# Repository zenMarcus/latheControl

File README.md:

# latheControl
lathe controller and HMI for cowells restoration project

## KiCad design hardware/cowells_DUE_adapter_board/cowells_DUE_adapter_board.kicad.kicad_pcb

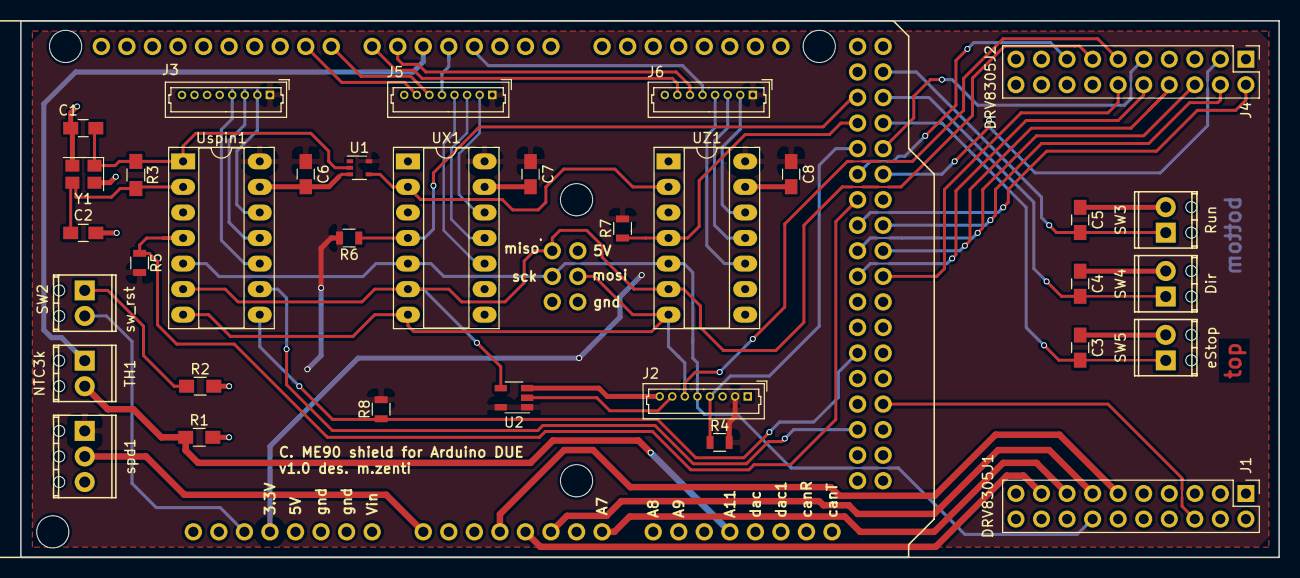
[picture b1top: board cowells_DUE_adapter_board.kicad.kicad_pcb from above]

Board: 2 copper layers, 125.1 x 53.3 mm, 35 parts (0 on the bottom side), 52 nets.

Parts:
C1, C2: 18p; C_0805_HandSoldering
C3, C4, C5: 15n; C_0805_HandSoldering
C6, C7, C8: 0.1uF; C_0805_HandSoldering
J1: DRV8305J1; Pin_Header_Straight_2x10_Pitch2.54mm
J2: AS5048A; Molex_PicoBlade_53047-0810_08x1.25mm_Straight
J3: spindl enc.; Molex_PicoBlade_53047-0810_08x1.25mm_Straight
J4: DRV8305J2; Pin_Header_Straight_2x10_Pitch2.54mm
J5, J6: AS5311AB; Molex_PicoBlade_53047-0810_08x1.25mm_Straight
R1: 1k; R_0805_HandSoldering
R2: 10k; R_0805_HandSoldering
R3: 1M; R_0805_HandSoldering
R4, R5, R6, R7, R8: 10k; R_0805
SW2: sw_rst; TerminalBlock_Phoenix_MPT-2.54mm_2pol
SW3: Run; TerminalBlock_Phoenix_MPT-2.54mm_2pol
SW4: Dir; TerminalBlock_Phoenix_MPT-2.54mm_2pol
SW5: eStop; TerminalBlock_Phoenix_MPT-2.54mm_2pol
TH1: NTC3k; TerminalBlock_Phoenix_MPT-2.54mm_2pol
U1: NL17SZ14; SOT-353_SC-70-5
U2: 74AHC1G125; TSOT-23-5
UX1: LS7366R; DIP-14_W7.62mm_Socket_LongPads
UZ1: LS7366R; DIP-14_W7.62mm_Socket_LongPads
Uspin1: LS7366R; DIP-14_W7.62mm_Socket_LongPads
XA1: Arduino_Due_Shield; Arduino_Due_Shield_drv8305
Y1: 10MHz; Crystal_SMD_3225-4pin_3.2x2.5mm
spd1: 5k; TerminalBlock_Phoenix_MPT-2.54mm_3pol

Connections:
/ClkX: J5.6, XA1.D8
/ClkZ: J6.6, XA1.D6
/CsnMot: J2.4, R4.1, XA1.D28
/CsnX: J5.5, XA1.D4
/CsnZ: J6.5, XA1.D3
/DoX: J5.7, XA1.D9
/DoZ: J6.7, XA1.D7
/ENGate: J4.15, XA1.D30
/InH_A: J4.2, XA1.D34
/InH_B: J4.6, XA1.D36
/InH_C: J4.10, XA1.D38
/InL_A: J4.4, XA1.D35
/InL_B: J4.8, XA1.D37
/InL_C: J4.12, XA1.D39
/IsenA: J1.13, XA1.A5
/IsenB: J1.15, XA1.A7
/IsenC: J1.17, XA1.A4
/MISO: J4.13, U2.4, UX1.6, UZ1.6, Uspin1.6, XA1.MISO
/MOSI: J2.6, J4.11, UX1.7, UZ1.7, Uspin1.7, XA1.MOSI
/PWRGD: J4.9, XA1.D29
/SCK: J1.14, J2.5, UX1.5, UZ1.5, Uspin1.5, XA1.SCK
/SCS: J4.3, XA1.D31
/SS_spin: R5.1, Uspin1.4, XA1.D32
/SS_x: R6.1, UX1.4, XA1.D24
/SS_z: R7.1, UZ1.4, XA1.D26
/SpnDFLAG: Uspin1.9, XA1.D50
/SpnLFLAG: R8.1, Uspin1.8, XA1.D44
/TH1: R1.1, TH1.2, XA1.A11
/Th1Ex: TH1.1, XA1.D5
/Vsen_PVDD: J1.11, XA1.A3
/nFAULT: J1.6, XA1.D49
/speed: XA1.A0, spd1.2
GND: C1.2, C2.2, C3.1, C4.1, C5.1, C6.2, C7.2, C8.2, J1.3, J2.8, J3.6, J3.8, J4.1, J5.8, J6.8, R1.2, R2.2, SW3.2, SW4.2, SW5.2, U1.3, U2.3, UX1.3, UX1.13, UZ1.3, UZ1.13, Uspin1.3, Uspin1.13, XA1.GND1, XA1.GND2, XA1.GND3, XA1.GND4, XA1.GND5, XA1.GND6, Y1.2, Y1.4, spd1.3
unnamed: C1.1, R3.1, U1.2, Uspin1.1, Y1.1
unnamed: C2.1, R3.2, Uspin1.2, Y1.3
unnamed: C3.2, SW5.1, XA1.D27
unnamed: C4.2, SW4.1, XA1.D25
unnamed: C5.2, SW3.1, XA1.D23
unnamed: J2.7, U2.2
unnamed: J3.2, Uspin1.12
unnamed: J3.3, Uspin1.11
unnamed: J3.4, Uspin1.10
unnamed: J5.2, UX1.12
unnamed: J5.3, UX1.11
unnamed: J5.4, UX1.10
unnamed: J6.2, UZ1.12
unnamed: J6.3, UZ1.11
unnamed: J6.4, UZ1.10
unnamed: R2.1, SW2.1
unnamed: SW2.2, XA1.RST1
unnamed: U1.4, UX1.2, UZ1.2
VCC: C6.1, C7.1, C8.1, J2.2, J3.1, J5.1, J6.1, R4.2, R5.2, R6.2, R7.2, R8.2, U1.5, U2.1, U2.5, UX1.14, UZ1.14, Uspin1.14, XA1.3V3, spd1.1

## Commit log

2018-02-26 first commit
    all project files
2018-05-10 implemented current reading
    current reading updated
2019-03-10 total refactor for platform IO
2019-03-10 as5048 comment added
2019-03-19 ...working on current measurements
2019-04-11 complete refactore - sync pwm_adc
2021-02-17 just pickin up the project again
2021-02-21 minor improvements
2021-02-21 foc now run on int math 6x faster
2021-02-25 encoder mapping and linearization WIP
2021-02-26 added encoder linearity compensation
2021-03-07 lot's of small improvements
2021-03-09 clark and park xform implemented (to be validated)
2021-03-11 changed motor phase sequence fro easier FOC debug
2021-03-15 Foc, SVM and PIDs now working. lots to cleanup
2021-03-20 fixed PID and rotor alignament
2021-03-31 cleanup of old code
